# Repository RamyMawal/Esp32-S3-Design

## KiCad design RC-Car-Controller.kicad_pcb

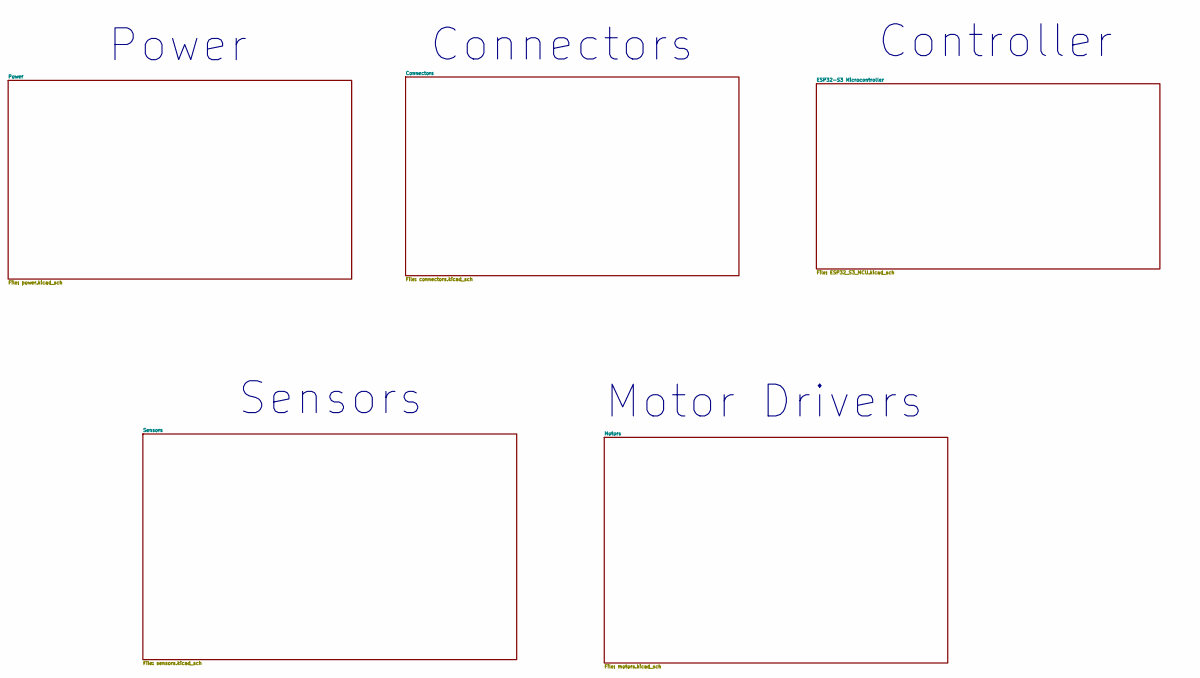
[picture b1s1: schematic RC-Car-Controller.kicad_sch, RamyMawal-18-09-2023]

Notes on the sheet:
Motor Drivers
Sensors
Controller
Connectors
Power

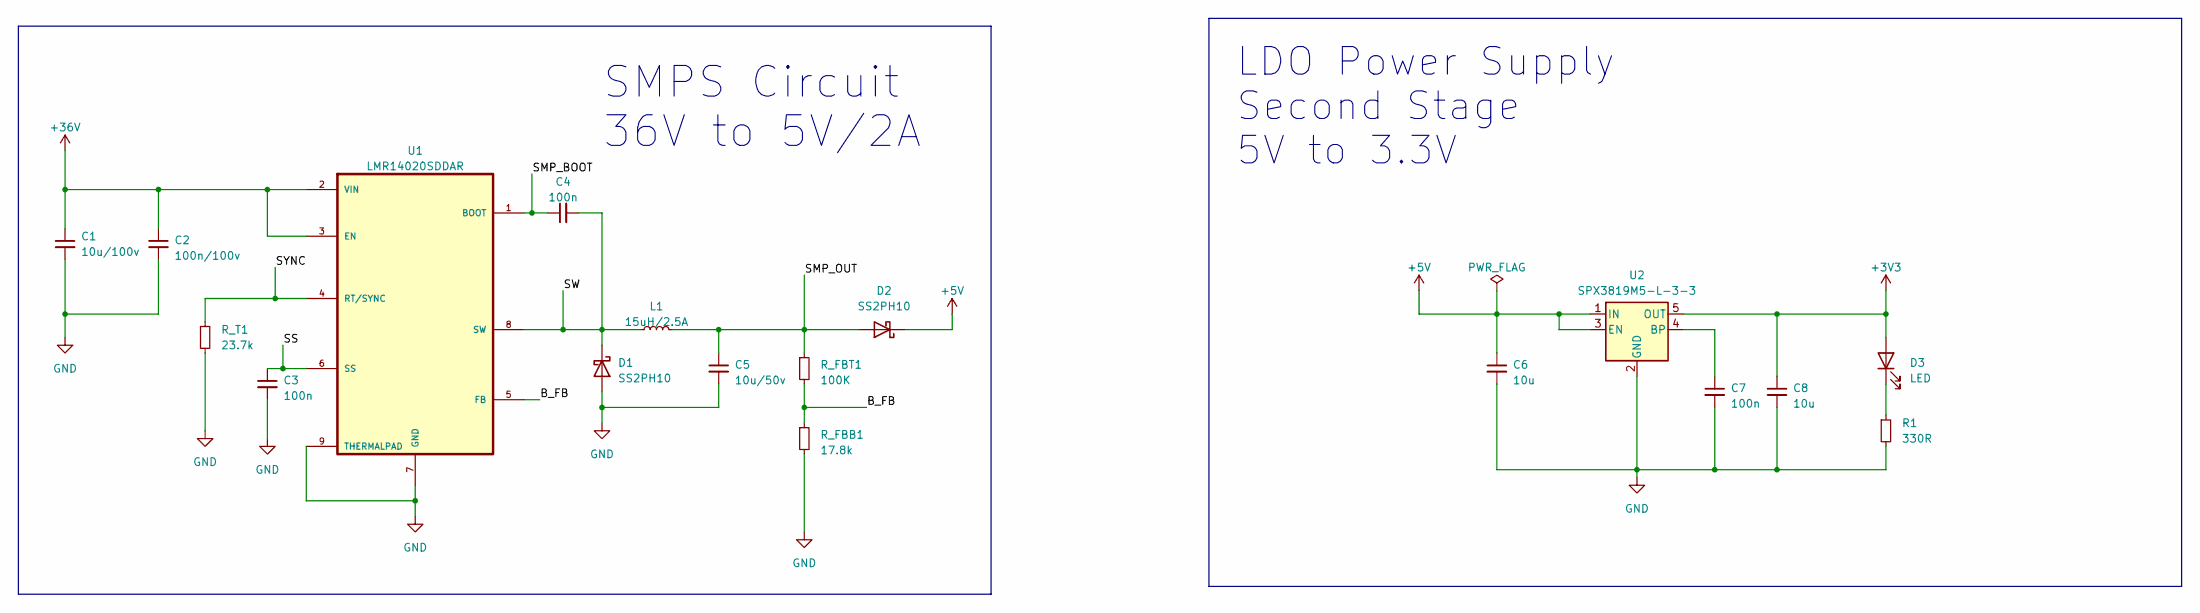
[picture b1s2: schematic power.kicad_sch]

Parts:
C1: 10u/100v; C_1210_3225Metric; LCSC C5156756
C2: 100n/100v; C_0603_1608Metric; LCSC C88219
C3, C4, C7: 100n; C_0402_1005Metric
C5: 10u/50v; C_1210_3225Metric; LCSC C72487
C6, C8: 10u; C_0603_1608Metric
D1, D2: SS2PH10; DO-220AA_SS2PH10-M3&slash_84A_VIS
D3: LED; LED_0603_1608Metric
L1: 15uH/2.5A; L_Bourns_SRN6045TA; LCSC C404502
R1: 330R; R_0603_1608Metric
R_FBB1: 17.8k; R_0603_1608Metric
R_FBT1: 100K; R_0603_1608Metric
R_T1: 23.7k; R_0603_1608Metric
U1: LMR14020SDDAR; VREG_LM5017MR_NOPB
U2: SPX3819M5-L-3-3; SOT-23-5; LCSC C9055

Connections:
+3V3: C8.1, D3.2 (A), U2.5 (OUT); also elsewhere on the board
+5V: C6.1, D2.1 (K), U2.1 (IN), U2.3 (EN); also elsewhere on the board
+36V: C1.1, C2.1, U1.2 (VIN), U1.3 (EN); also elsewhere on the board
/Power/B_FB: R_FBB1.1, R_FBT1.2, U1.5 (FB)
/Power/SMP_BOOT: C4.1, U1.1 (BOOT)
/Power/SMP_OUT: C5.1, D2.2 (A), L1.2, R_FBT1.1
/Power/SS: C3.1, U1.6 (SS)
/Power/SW: C4.2, D1.1 (K), L1.1, U1.8 (SW)
/Power/SYNC: R_T1.1, U1.4 (RT/SYNC)
GND: C1.2, C2.2, C3.2, C5.2, C6.2, C7.2, C8.2, D1.2 (A), R1.2, R_FBB1.2, R_T1.2, U1.7 (GND), U1.9 (THERMALPAD), U2.2 (GND); also elsewhere on the board
unnamed: D3.1 (K), R1.1
unnamed: C7.1, U2.4 (BP)

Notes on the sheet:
SMPS Circuit 36V to 5V/2A
LDO Power Supply Second Stage 5V to 3.3V

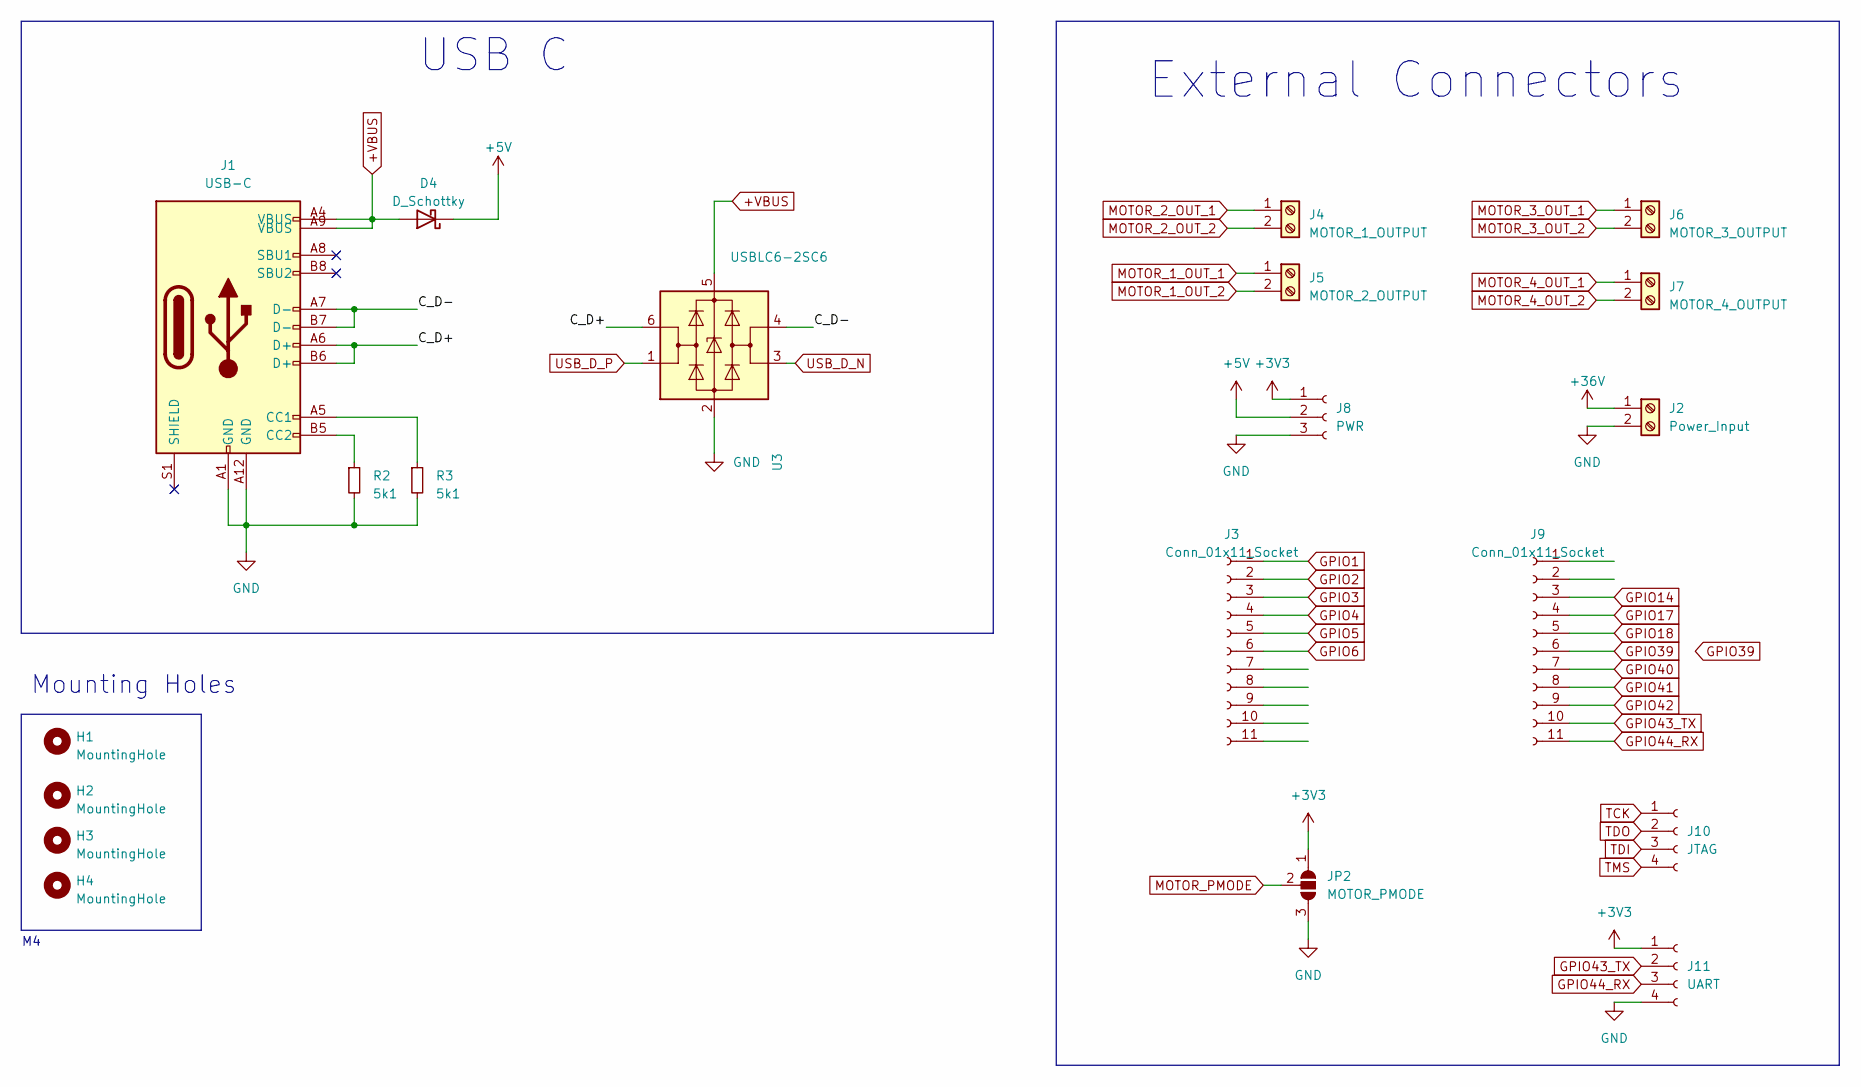
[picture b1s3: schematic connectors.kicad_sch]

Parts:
D4: D_Schottky; DO-220AA_SS2PH10-M3&slash_84A_VIS
H1, H2, H3, H4: MountingHole; MountingHole_4.3mm_M4
J1: USB-C; USB_C_Receptacle_HRO_TYPE-C-31-M-12
J2: Power_Input; TerminalBlock_bornier-2_P5.08mm
J3: Conn_01x11_Socket; PinHeader_1x11_P2.54mm_Vertical_SMD_Pin1Left
J4: MOTOR_1_OUTPUT; TerminalBlock_bornier-2_P5.08mm
J5: MOTOR_2_OUTPUT; TerminalBlock_bornier-2_P5.08mm
J6: MOTOR_3_OUTPUT; TerminalBlock_bornier-2_P5.08mm
J7: MOTOR_4_OUTPUT; TerminalBlock_bornier-2_P5.08mm
J8: PWR; PinSocket_1x03_P2.54mm_Vertical
J9: Conn_01x11_Socket; PinHeader_1x11_P2.54mm_Vertical
J10: JTAG; PinHeader_1x04_P2.54mm_Vertical_SMD_Pin1Right
J11: UART; PinHeader_1x04_P2.54mm_Vertical_SMD_Pin1Right
JP2: MOTOR_PMODE; SolderJumper-3_P2.0mm_Open_TrianglePad1.0x1.5mm
R2, R3: 5k1; R_0603_1608Metric
U3: USBLC6-2SC6; SOT-23-6

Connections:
+3V3: J8.1, J11.1, JP2.1 (A); also elsewhere on the board
+5V: D4.1 (K), J8.2; also elsewhere on the board
+36V: J2.1; also elsewhere on the board
+VBUS: D4.2 (A), J1.A4 (VBUS), J1.A9 (VBUS), J1.B4 (VBUS), J1.B9 (VBUS), U3.5 (VBUS)
/Connectors/C_D+: J1.A6 (D+), J1.B6 (D+), U3.6 (I/O1)
/Connectors/C_D-: J1.A7 (D-), J1.B7 (D-), U3.4 (I/O2)
GND: J1.A1 (GND), J1.A12 (GND), J1.B1 (GND), J1.B12 (GND), J2.2, J8.3, J11.4, JP2.3 (B), R2.2, R3.2, U3.2 (GND); also elsewhere on the board
GPIO1: J3.1
GPIO2: J3.2
GPIO3: J3.3
GPIO4: J3.4
GPIO5: J3.5
GPIO6: J3.6
GPIO14: J9.3
GPIO17: J9.4
GPIO18: J9.5
GPIO39: J9.6
GPIO40: J9.7
GPIO41: J9.8
GPIO42: J9.9
GPIO43_TX: J9.10, J11.2; also elsewhere on the board
GPIO44_RX: J9.11, J11.3; also elsewhere on the board
MOTOR_1_OUT_1: J5.1; also elsewhere on the board
MOTOR_1_OUT_2: J5.2; also elsewhere on the board
MOTOR_2_OUT_1: J4.1; also elsewhere on the board
MOTOR_2_OUT_2: J4.2; also elsewhere on the board
MOTOR_3_OUT_1: J6.1; also elsewhere on the board
MOTOR_3_OUT_2: J6.2; also elsewhere on the board
MOTOR_4_OUT_1: J7.1; also elsewhere on the board
MOTOR_4_OUT_2: J7.2; also elsewhere on the board
MOTOR_PMODE: JP2.2 (C); also elsewhere on the board
unnamed: J1.A5 (CC1), R3.1
unnamed: J1.B5 (CC2), R2.1
TCK: J10.1; also elsewhere on the board
TDI: J10.3; also elsewhere on the board
TDO: J10.2; also elsewhere on the board
TMS: J10.4; also elsewhere on the board
USB_D_N: U3.3 (I/O2); also elsewhere on the board
USB_D_P: U3.1 (I/O1); also elsewhere on the board

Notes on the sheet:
External Connectors
Mounting Holes
USB C

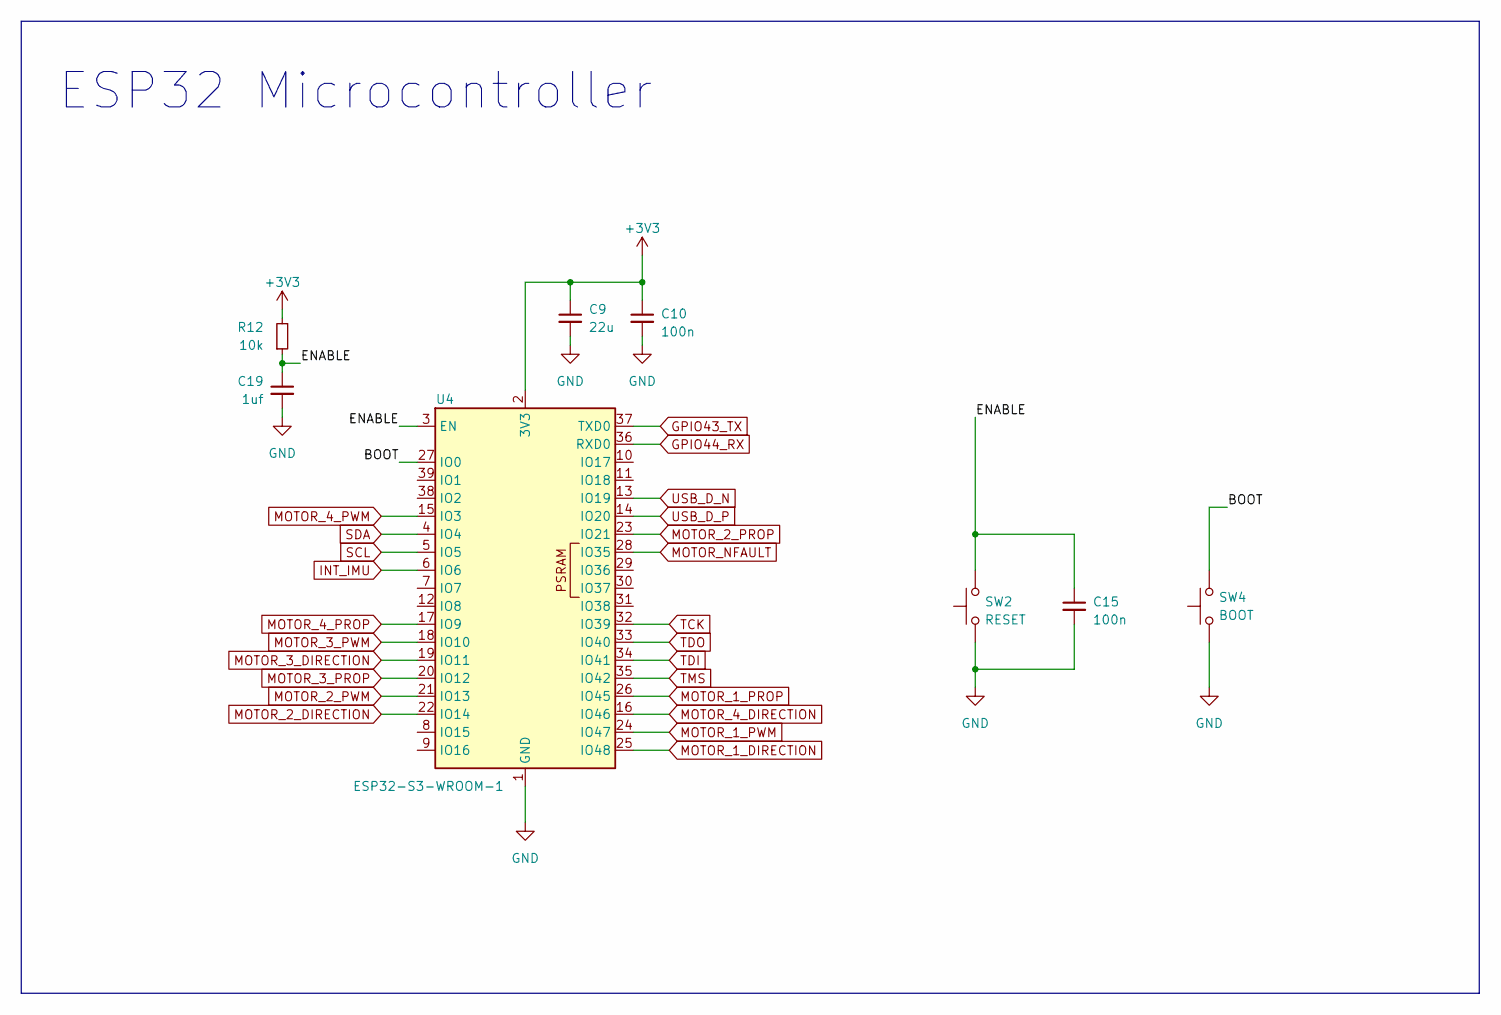
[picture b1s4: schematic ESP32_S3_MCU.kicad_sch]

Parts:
C9: 22u; C_0402_1005Metric
C10, C15: 100n; C_0402_1005Metric
C19: 1uf; C_0402_1005Metric
R12: 10k; R_0603_1608Metric
SW2: RESET; SW_Push_SPST_NO_Alps_SKRK
SW4: BOOT; SW_Push_SPST_NO_Alps_SKRK
U4: ESP32-S3-WROOM-1

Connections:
+3V3: C9.1, C10.1, R12.2, U4.2 (3V3); also elsewhere on the board
/ESP32-S3 Microcontroller /BOOT: SW4.2, U4.27 (IO0); also elsewhere on the board
/ESP32-S3 Microcontroller /ENABLE: C15.1, C19.1, R12.1, SW2.2, U4.3 (EN)
GND: C9.2, C10.2, C15.2, C19.2, SW2.1, SW4.1, U4.1 (GND), U4.40 (GND), U4.41 (GND); also elsewhere on the board
GPIO43_TX: U4.37 (TXD0); also elsewhere on the board
GPIO44_RX: U4.36 (RXD0); also elsewhere on the board
INT_IMU: U4.6 (IO6); also elsewhere on the board
MOTOR_1_DIRECTION: U4.25 (IO48); also elsewhere on the board
MOTOR_1_PROP: U4.26 (IO45); also elsewhere on the board
MOTOR_1_PWM: U4.24 (IO47); also elsewhere on the board
MOTOR_2_DIRECTION: U4.22 (IO14); also elsewhere on the board
MOTOR_2_PROP: U4.23 (IO21); also elsewhere on the board
MOTOR_2_PWM: U4.21 (IO13); also elsewhere on the board
MOTOR_3_DIRECTION: U4.19 (IO11); also elsewhere on the board
MOTOR_3_PROP: U4.20 (IO12); also elsewhere on the board
MOTOR_3_PWM: U4.18 (IO10); also elsewhere on the board
MOTOR_4_DIRECTION: U4.16 (IO46); also elsewhere on the board
MOTOR_4_PROP: U4.17 (IO9); also elsewhere on the board
MOTOR_4_PWM: U4.15 (IO3); also elsewhere on the board
MOTOR_NFAULT: U4.28 (IO35); also elsewhere on the board
SCL: U4.5 (IO5); also elsewhere on the board
SDA: U4.4 (IO4); also elsewhere on the board
TCK: U4.32 (IO39); also elsewhere on the board
TDI: U4.34 (IO41); also elsewhere on the board
TDO: U4.33 (IO40); also elsewhere on the board
TMS: U4.35 (IO42); also elsewhere on the board
USB_D_N: U4.13 (IO19); also elsewhere on the board
USB_D_P: U4.14 (IO20); also elsewhere on the board

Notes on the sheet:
ESP32 Microcontroller

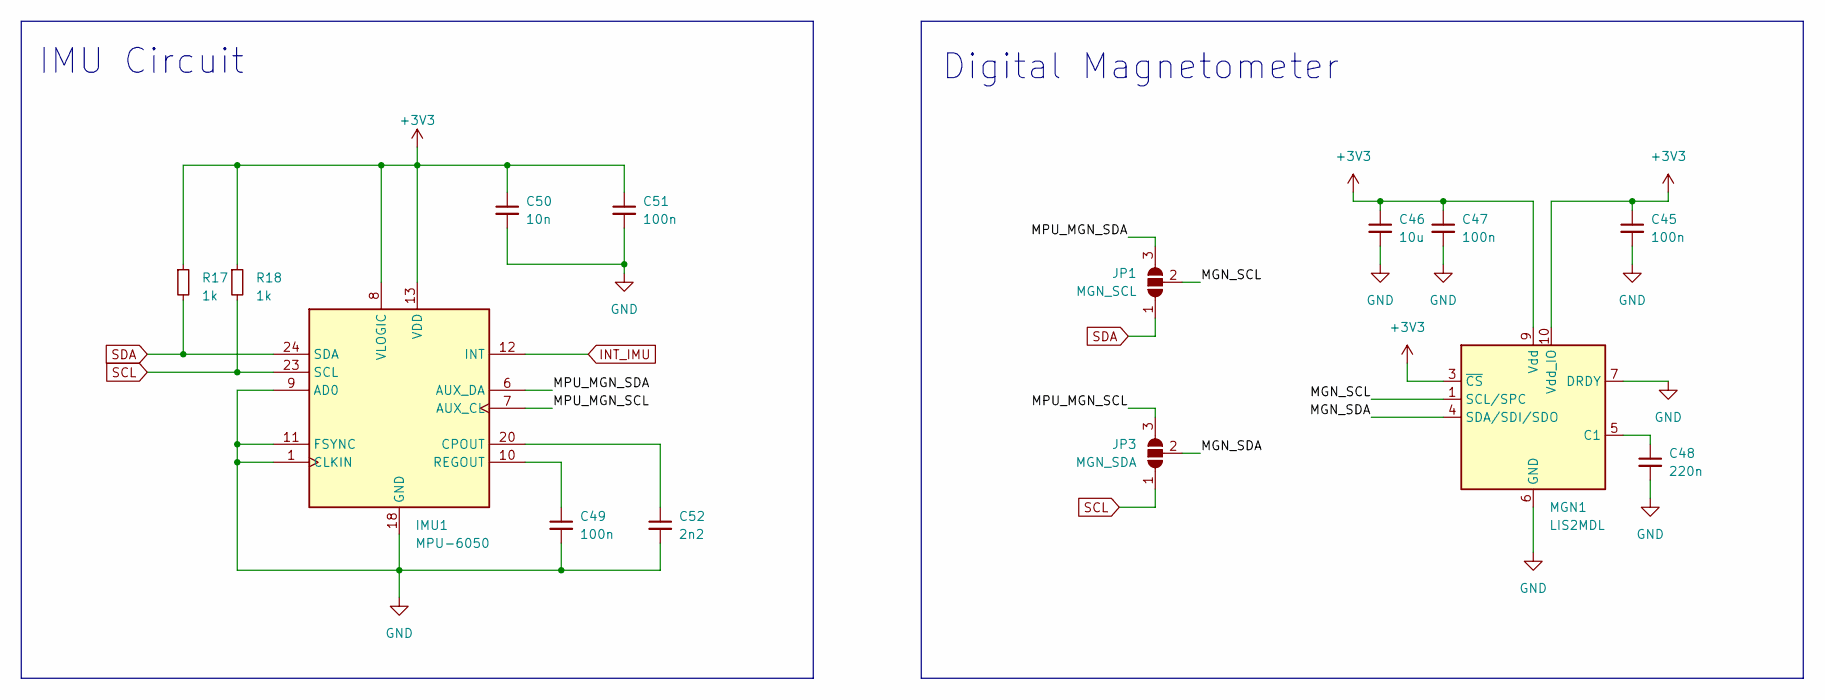
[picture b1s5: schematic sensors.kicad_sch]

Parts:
C45, C47, C49, C51: 100n; C_0402_1005Metric
C46: 10u; C_0603_1608Metric
C48: 220n; C_0402_1005Metric
C50: 10n; C_0402_1005Metric
C52: 2n2; C_0402_1005Metric
IMU1: MPU-6050; InvenSense_QFN-24_4x4mm_P0.5mm; LCSC C24112
JP1: MGN_SCL; SolderJumper-3_P2.0mm_Open_TrianglePad1.0x1.5mm
JP3: MGN_SDA; SolderJumper-3_P2.0mm_Open_TrianglePad1.0x1.5mm
MGN1: LIS2MDL; LGA-12_2x2mm_P0.5mm; LCSC C919695
R17, R18: 1k; R_0402_1005Metric

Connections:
+3V3: C45.1, C46.1, C47.1, C50.1, C51.1, IMU1.8 (VLOGIC), IMU1.13 (VDD), MGN1.3 (~CS), MGN1.9 (Vdd), MGN1.10 (Vdd_IO), R17.1, R18.1; also elsewhere on the board
/Sensors/MGN_SCL: JP1.2 (C), MGN1.1 (SCL/SPC)
/Sensors/MGN_SDA: JP3.2 (C), MGN1.4 (SDA/SDI/SDO)
/Sensors/MPU_MGN_SCL: IMU1.7 (AUX_CL), JP3.3 (B)
/Sensors/MPU_MGN_SDA: IMU1.6 (AUX_DA), JP1.3 (B)
GND: C45.2, C46.2, C47.2, C48.2, C49.2, C50.2, C51.2, C52.2, IMU1.1 (CLKIN), IMU1.9 (AD0), IMU1.11 (FSYNC), IMU1.18 (GND), MGN1.6 (GND), MGN1.7 (DRDY), MGN1.8 (GND); also elsewhere on the board
INT_IMU: IMU1.12 (INT); also elsewhere on the board
unnamed: C52.1, IMU1.20 (CPOUT)
unnamed: C49.1, IMU1.10 (REGOUT)
unnamed: C48.1, MGN1.5 (C1)
SCL: IMU1.23 (SCL), JP3.1 (A), R18.2; also elsewhere on the board
SDA: IMU1.24 (SDA), JP1.1 (A), R17.2; also elsewhere on the board

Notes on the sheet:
IMU Circuit
Digital Magnetometer

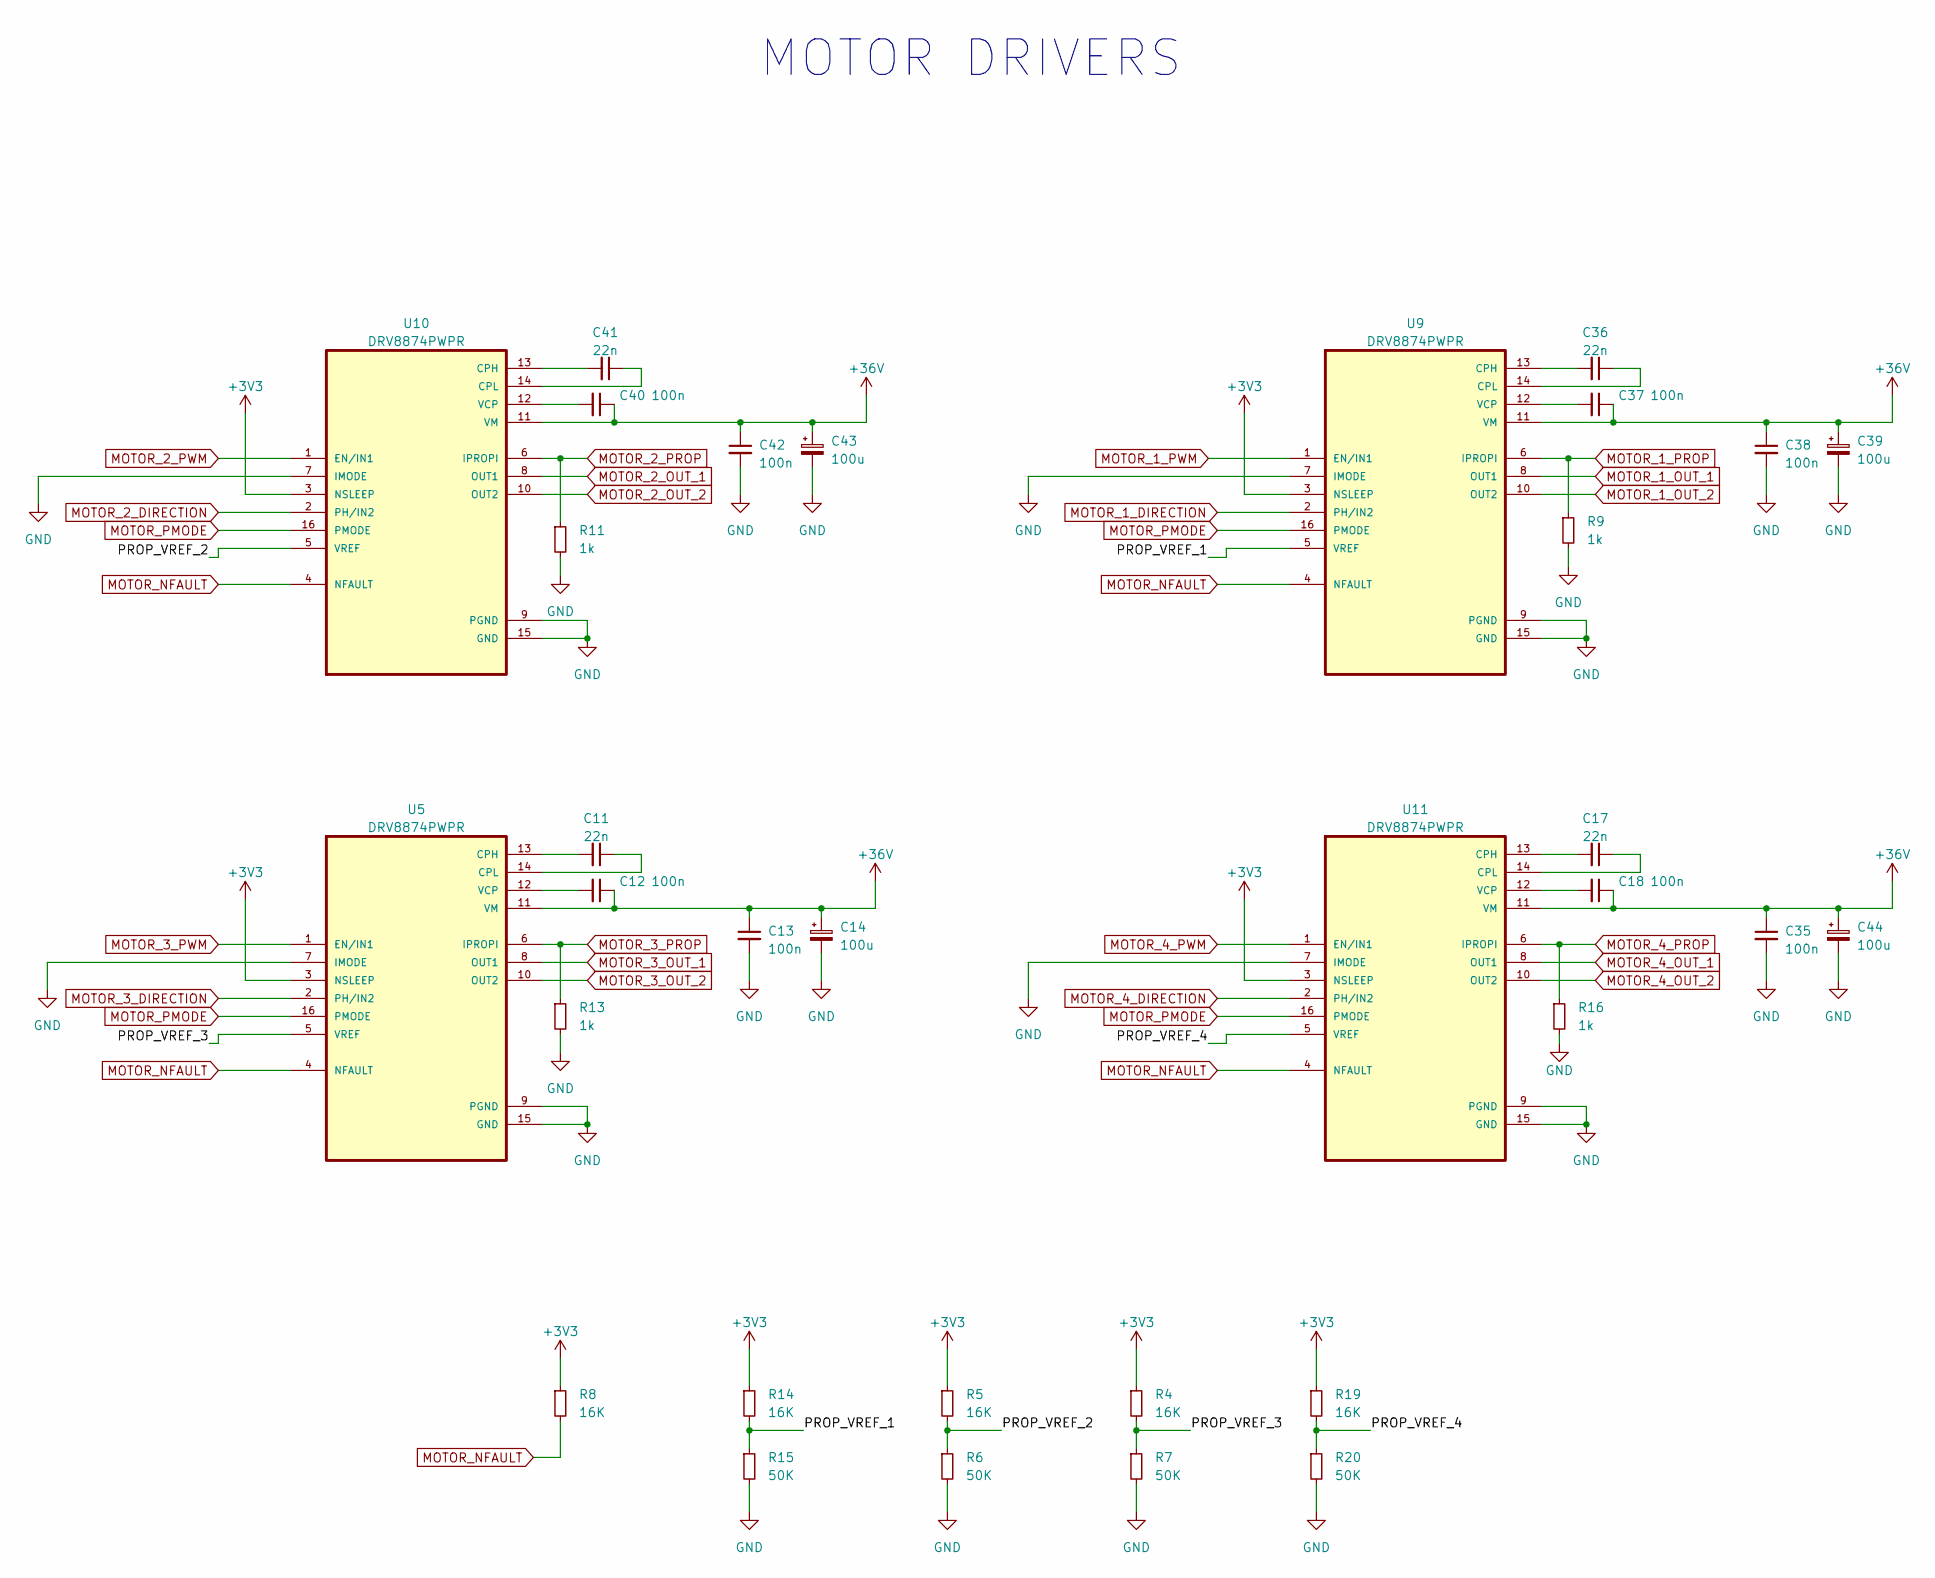
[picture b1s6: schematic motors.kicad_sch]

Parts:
C11, C17, C36, C41: 22n; C_0603_1608Metric; LCSC C561176
C12, C13, C18, C35, C37, C38, C40, C42: 100n; C_0402_1005Metric
C14, C39, C43, C44: 100u; CP_Elec_6.3x7.7
R4, R5, R8, R14, R19: 16K; R_0603_1608Metric
R6, R7, R15, R20: 50K; R_0603_1608Metric
R9, R11, R13, R16: 1k; R_0402_1005Metric
U5, U9, U10, U11: DRV8874PWPR; SOP65P640X120-17N; LCSC C1855818

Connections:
+3V3: R4.1, R5.1, R8.1, R14.1, R19.1, U5.3 (NSLEEP), U9.3 (NSLEEP), U10.3 (NSLEEP), U11.3 (NSLEEP); also elsewhere on the board
+36V: C12.1, C13.1, C14.1, C18.1, C35.1, C37.1, C38.1, C39.1, C40.1, C42.1, C43.1, C44.1, U5.11 (VM), U9.11 (VM), U10.11 (VM), U11.11 (VM); also elsewhere on the board
/Motors/PROP_VREF_1: R14.2, R15.1, U9.5 (VREF)
/Motors/PROP_VREF_2: R5.2, R6.1, U10.5 (VREF)
/Motors/PROP_VREF_3: R4.2, R7.1, U5.5 (VREF)
/Motors/PROP_VREF_4: R19.2, R20.1, U11.5 (VREF)
GND: C13.2, C14.2, C35.2, C38.2, C39.2, C42.2, C43.2, C44.2, R6.2, R7.2, R9.2, R11.2, R13.2, R15.2, R16.2, R20.2, U5.7 (IMODE), U5.9 (PGND), U5.15 (GND), U9.7 (IMODE), U9.9 (PGND), U9.15 (GND), U10.7 (IMODE), U10.9 (PGND), U10.15 (GND), U11.7 (IMODE), U11.9 (PGND), U11.15 (GND); also elsewhere on the board
MOTOR_1_DIRECTION: U9.2 (PH/IN2); also elsewhere on the board
MOTOR_1_OUT_1: U9.8 (OUT1); also elsewhere on the board
MOTOR_1_OUT_2: U9.10 (OUT2); also elsewhere on the board
MOTOR_1_PROP: R9.1, U9.6 (IPROPI); also elsewhere on the board
MOTOR_1_PWM: U9.1 (EN/IN1); also elsewhere on the board
MOTOR_2_DIRECTION: U10.2 (PH/IN2); also elsewhere on the board
MOTOR_2_OUT_1: U10.8 (OUT1); also elsewhere on the board
MOTOR_2_OUT_2: U10.10 (OUT2); also elsewhere on the board
MOTOR_2_PROP: R11.1, U10.6 (IPROPI); also elsewhere on the board
MOTOR_2_PWM: U10.1 (EN/IN1); also elsewhere on the board
MOTOR_3_DIRECTION: U5.2 (PH/IN2); also elsewhere on the board
MOTOR_3_OUT_1: U5.8 (OUT1); also elsewhere on the board
MOTOR_3_OUT_2: U5.10 (OUT2); also elsewhere on the board
MOTOR_3_PROP: R13.1, U5.6 (IPROPI); also elsewhere on the board
MOTOR_3_PWM: U5.1 (EN/IN1); also elsewhere on the board
MOTOR_4_DIRECTION: U11.2 (PH/IN2); also elsewhere on the board
MOTOR_4_OUT_1: U11.8 (OUT1); also elsewhere on the board
MOTOR_4_OUT_2: U11.10 (OUT2); also elsewhere on the board
MOTOR_4_PROP: R16.1, U11.6 (IPROPI); also elsewhere on the board
MOTOR_4_PWM: U11.1 (EN/IN1); also elsewhere on the board
MOTOR_NFAULT: R8.2, U5.4 (NFAULT), U9.4 (NFAULT), U10.4 (NFAULT), U11.4 (NFAULT); also elsewhere on the board
MOTOR_PMODE: U5.16 (PMODE), U9.16 (PMODE), U10.16 (PMODE), U11.16 (PMODE); also elsewhere on the board
unnamed: C11.2, U5.13 (CPH)
unnamed: C11.1, U5.14 (CPL)
unnamed: C12.2, U5.12 (VCP)
unnamed: C36.2, U9.13 (CPH)
unnamed: C36.1, U9.14 (CPL)
unnamed: C37.2, U9.12 (VCP)
unnamed: C41.2, U10.13 (CPH)
unnamed: C41.1, U10.14 (CPL)
unnamed: C40.2, U10.12 (VCP)
unnamed: C17.2, U11.13 (CPH)
unnamed: C17.1, U11.14 (CPL)
unnamed: C18.2, U11.12 (VCP)

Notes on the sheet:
MOTOR DRIVERS

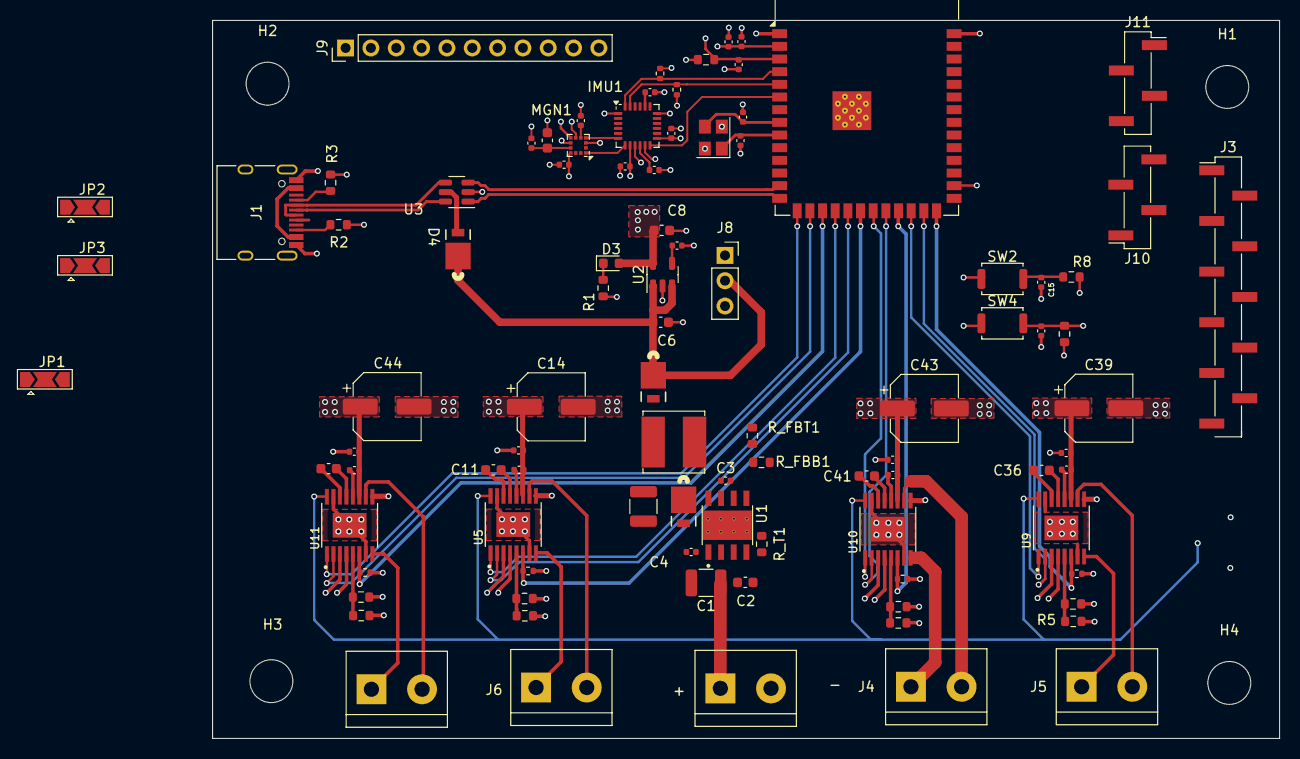
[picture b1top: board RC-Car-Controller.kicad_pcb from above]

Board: 4 copper layers, 107.0 x 72.0 mm, 98 parts (0 on the bottom side), 77 nets.

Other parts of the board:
C16: 100n; C_0402_1005Metric
C55, C56: 12p; C_0402_1005Metric
R10: 5k1; R_0603_1608Metric
X3: 32.768KHz; Crystal_SMD_3225-4Pin_3.2x2.5mm

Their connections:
+3V3: R10.1; also elsewhere on the board
/ESP32-S3 Microcontroller /BOOT: C16.1, R10.2; also elsewhere on the board
/ESP32-S3 Microcontroller /XTAL_N: C56.1, X3.1
/ESP32-S3 Microcontroller /XTAL_P: C55.1, X3.3
GND: C16.2, C55.2, C56.2, X3.2, X3.4; also elsewhere on the board

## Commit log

2023-11-24 Update placement
2024-01-07 route usb and flash
2024-01-09 add libraries folder
2024-01-10 Align mounting holes + edge cuts
2024-01-18 route motors
2024-03-14 before changing motors
2024-05-01 Add MPU6050 and LIS2MDL
2024-05-08 modify layout
2024-12-30 checkpoint for backup
2025-02-03 Checkpoint before updating MCU
2025-02-10 Replace MCU with WROOM-1 unit + route
2025-02-16 Route Motor Drivers
2025-02-21 Update capacitor footprints
2025-02-25 pcb updates & improvements
